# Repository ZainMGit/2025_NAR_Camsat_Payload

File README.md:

# 2025_NAR_CanSat_Payload
Download KiCAD_Camsat_PCB as a zip file and then open the project file within KiCAD to get the most up to date version of the pcb.

microsd pin orientation: 
-top view with pins pointing towards person and L to R- 
GND, VCC, MISO, MOSI, Sck, cs

9dof board
black wire - GND
Red - 3.3v 
blue- SDA
Yellow - SCL
order: BlaRBY

humidity - 
L to R with pins facing south
-GND, VCC, Signal

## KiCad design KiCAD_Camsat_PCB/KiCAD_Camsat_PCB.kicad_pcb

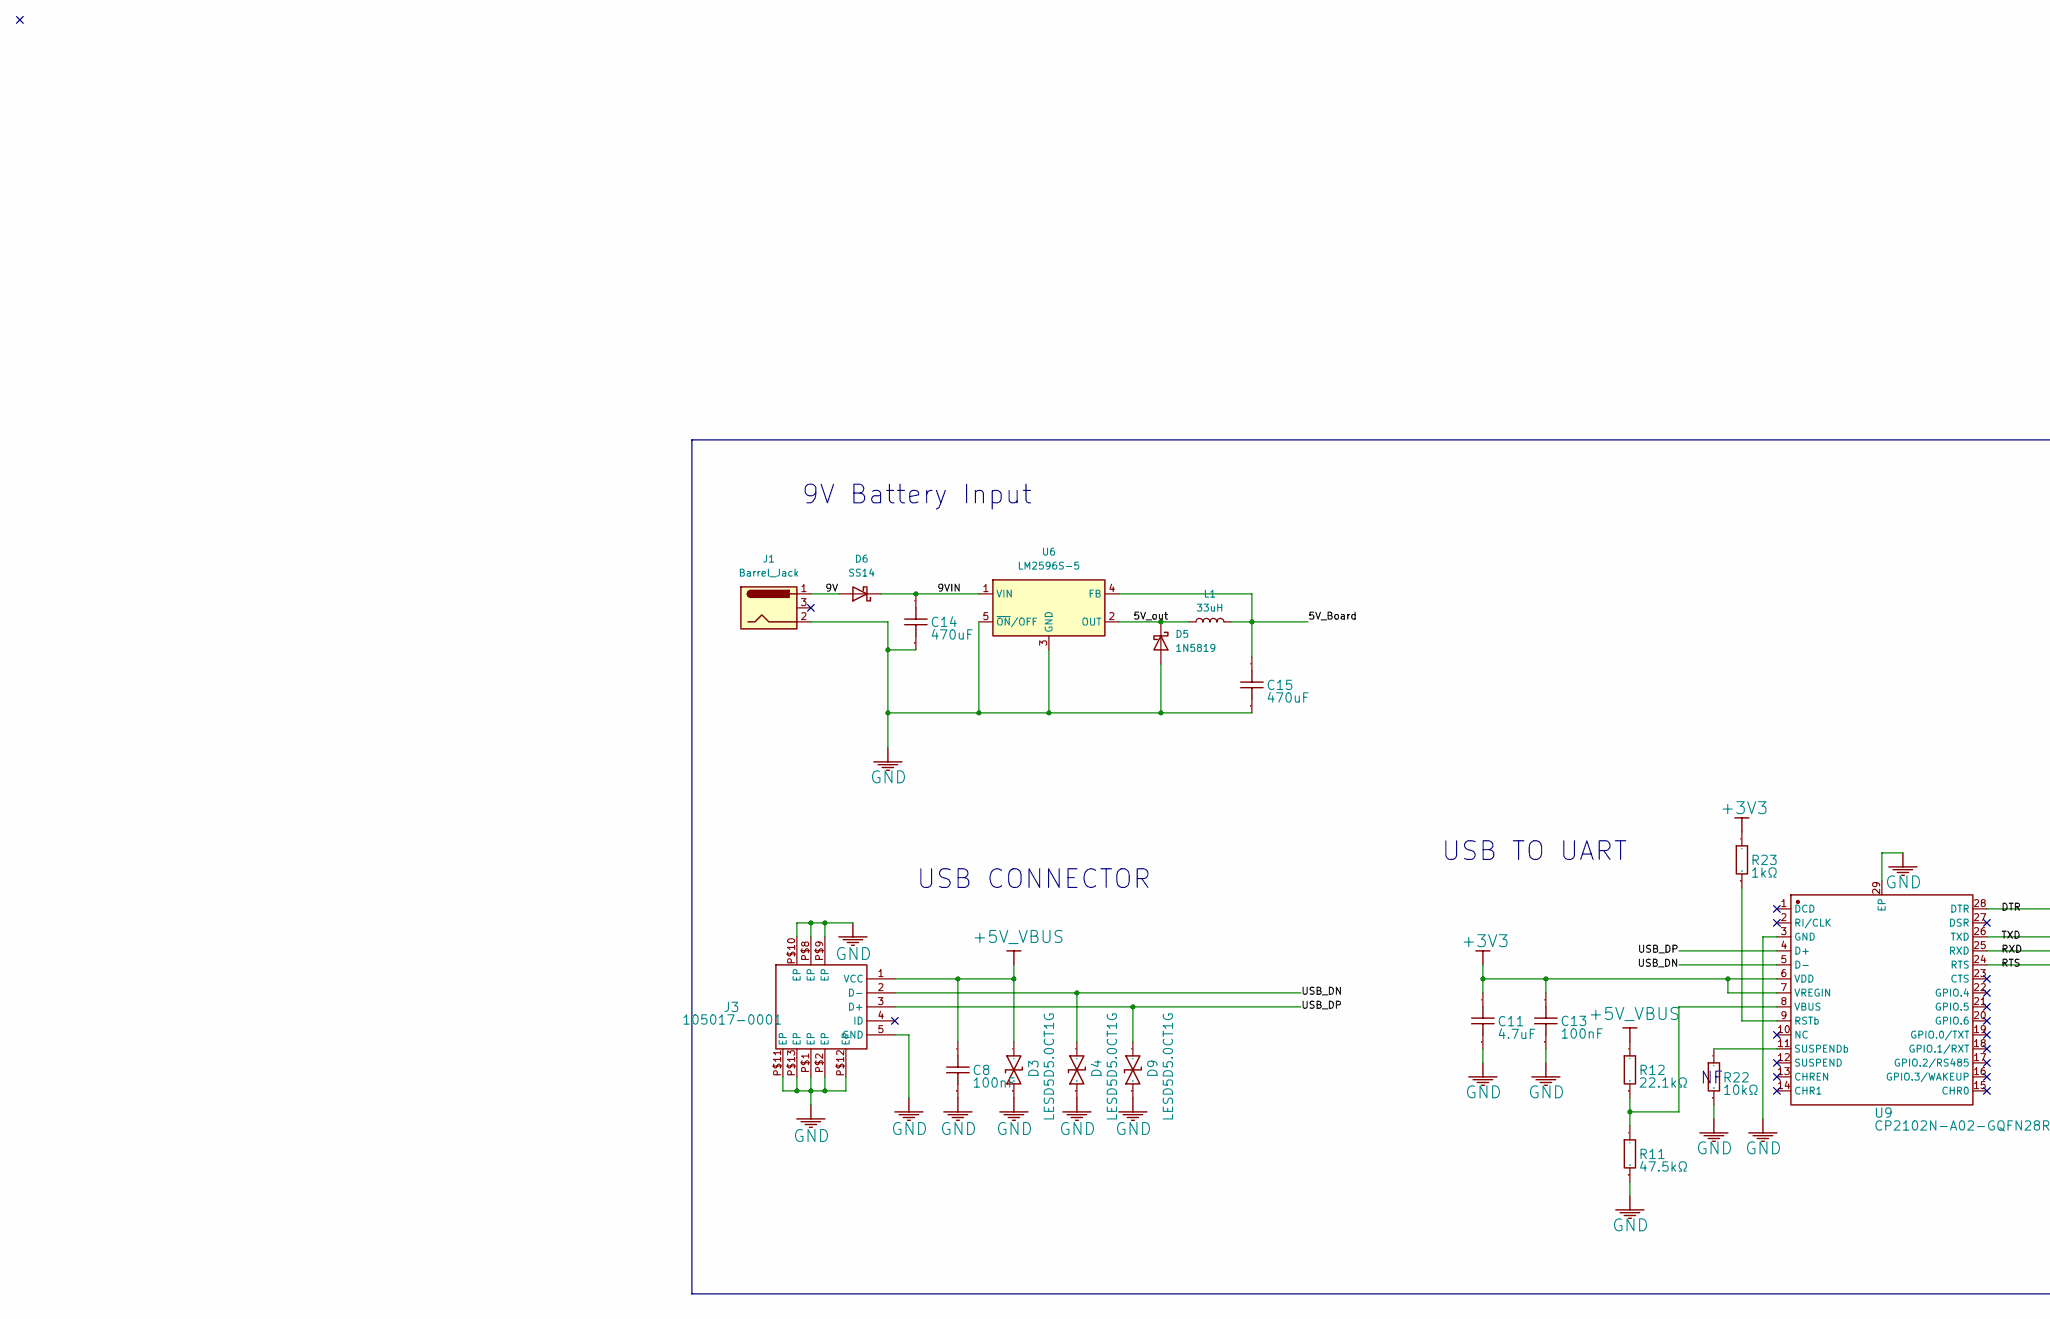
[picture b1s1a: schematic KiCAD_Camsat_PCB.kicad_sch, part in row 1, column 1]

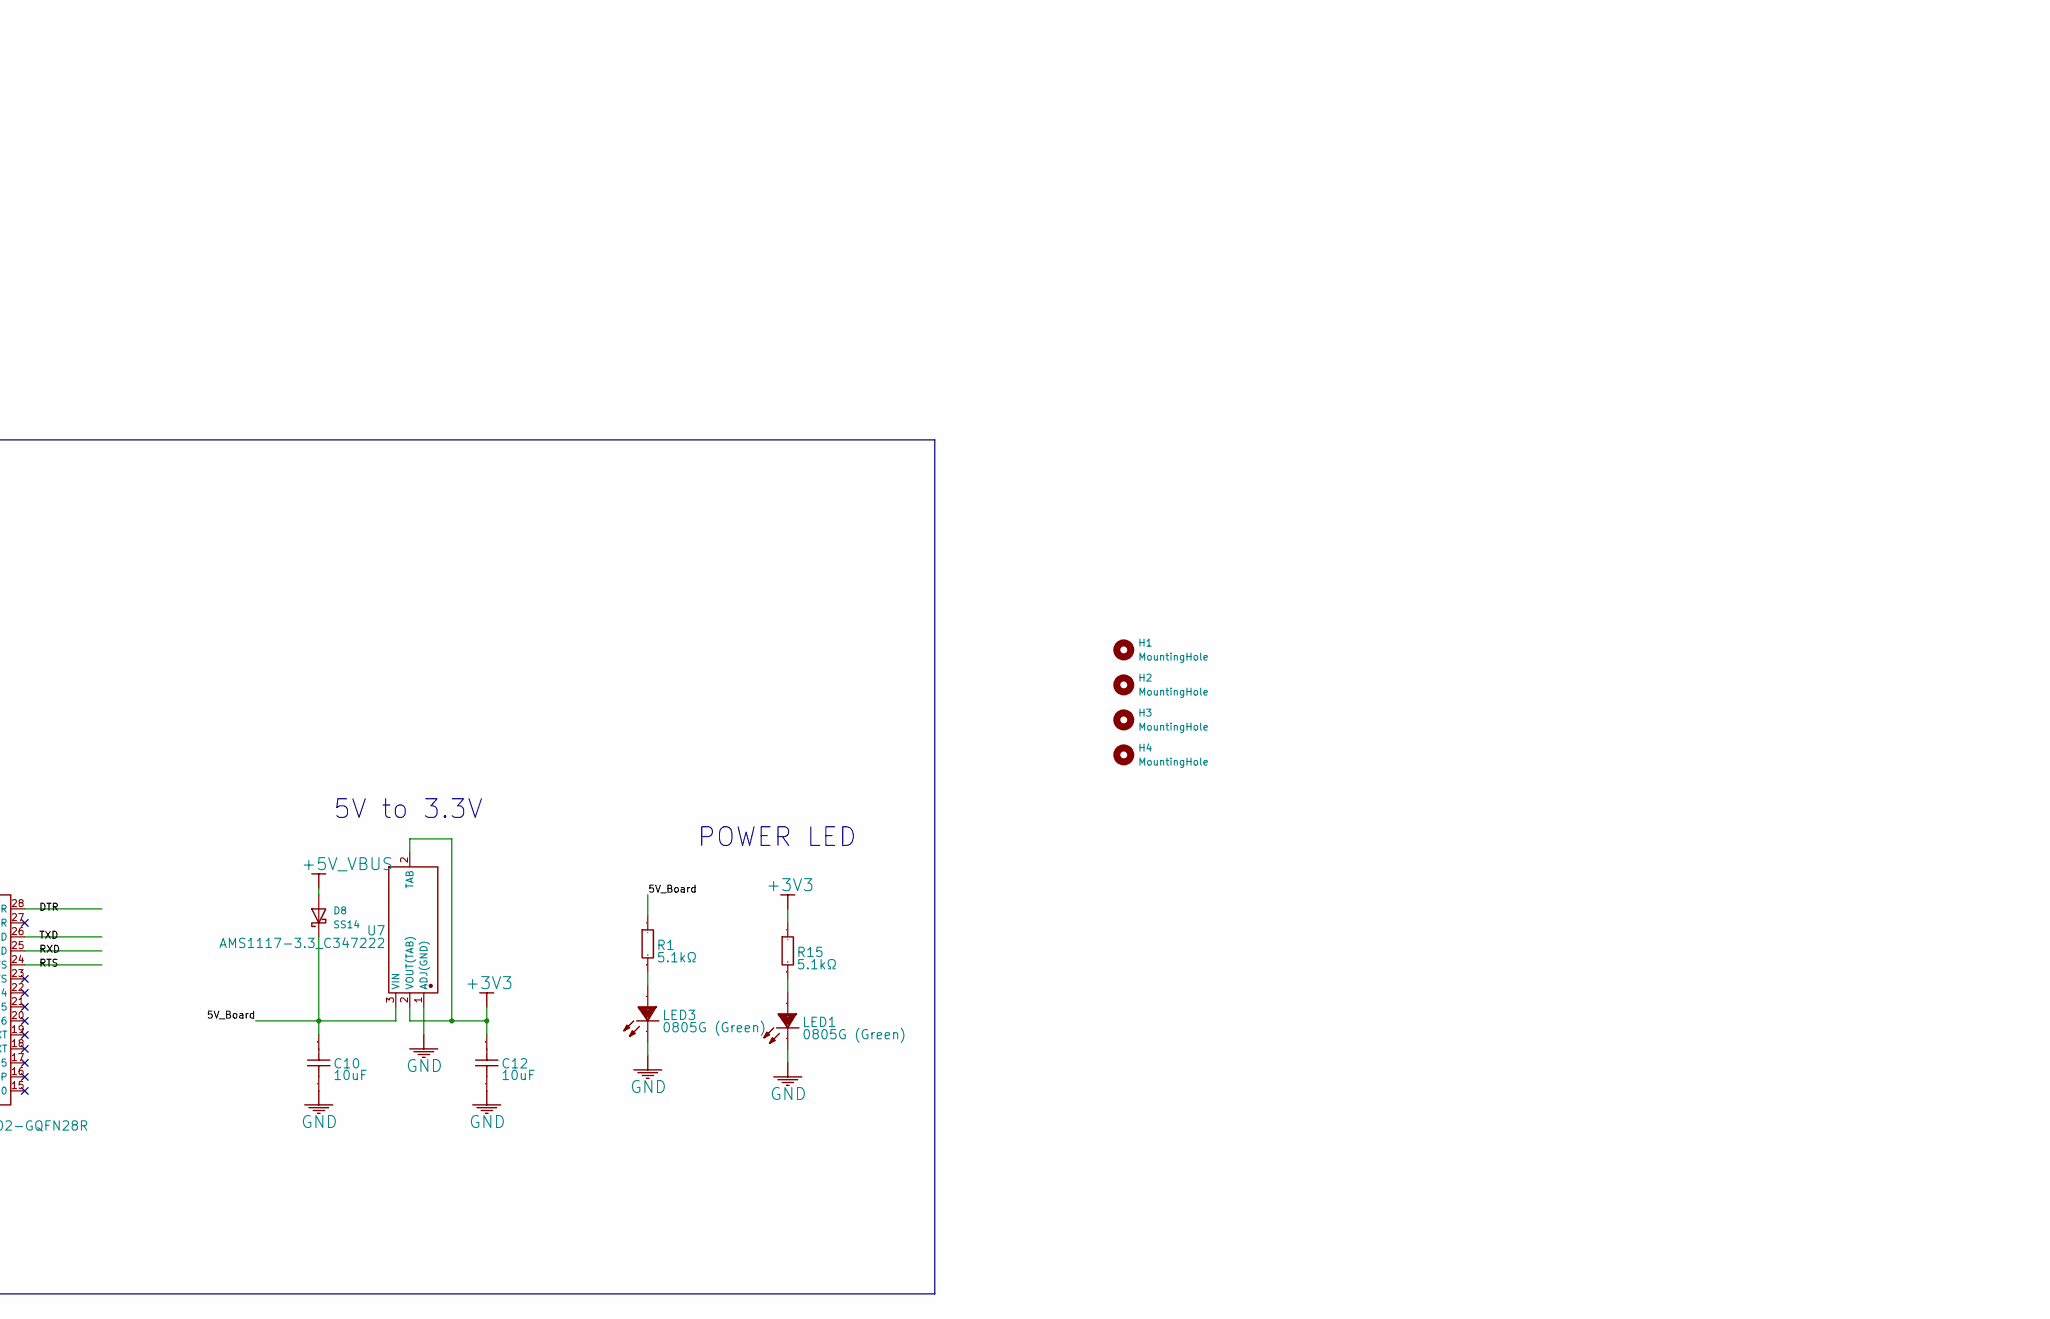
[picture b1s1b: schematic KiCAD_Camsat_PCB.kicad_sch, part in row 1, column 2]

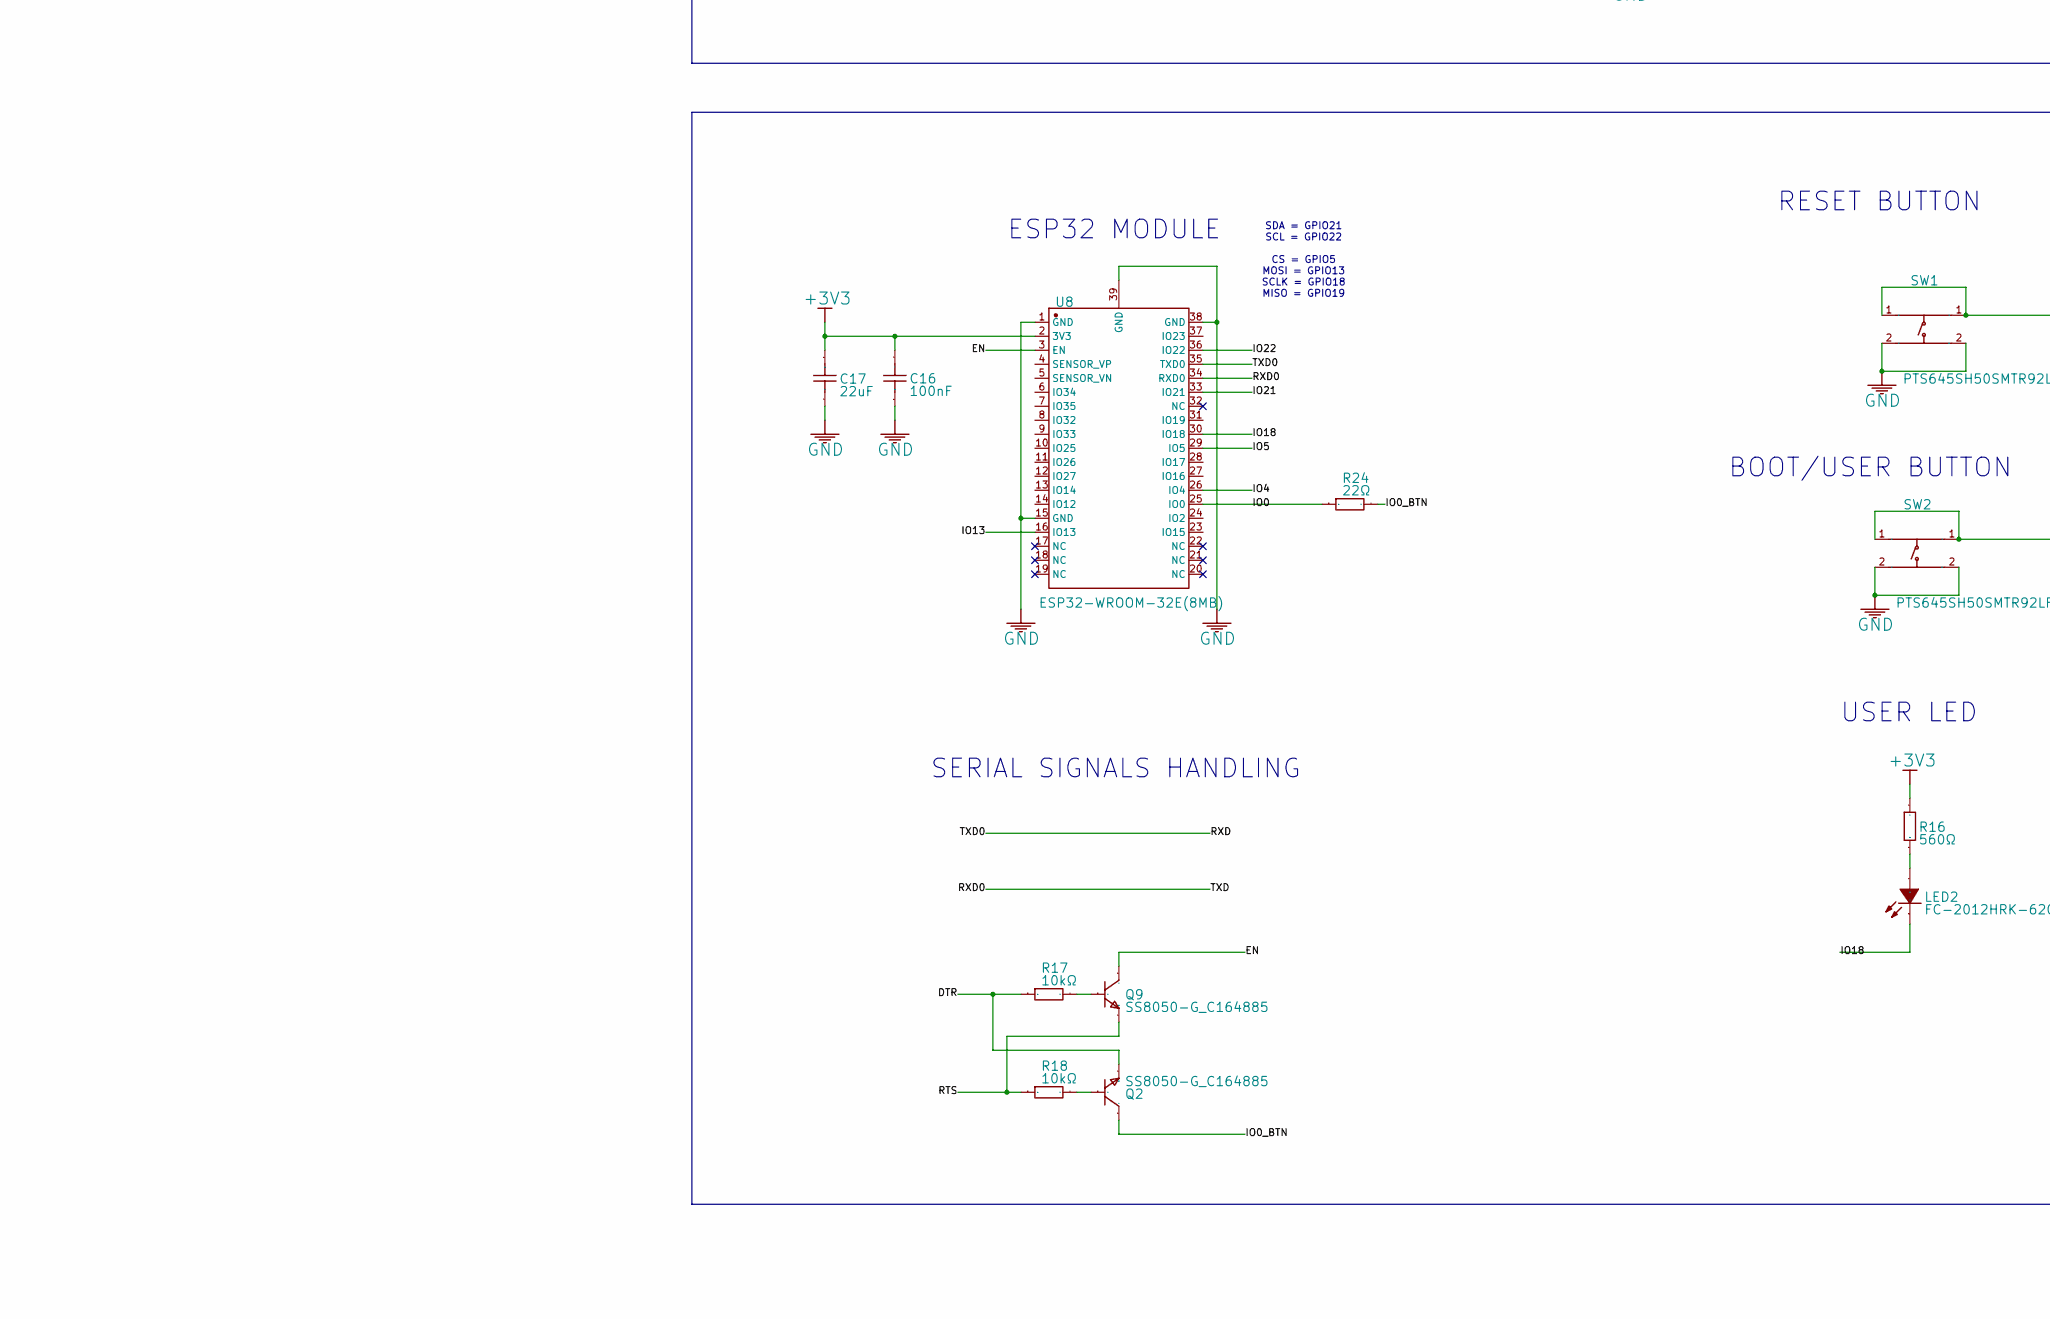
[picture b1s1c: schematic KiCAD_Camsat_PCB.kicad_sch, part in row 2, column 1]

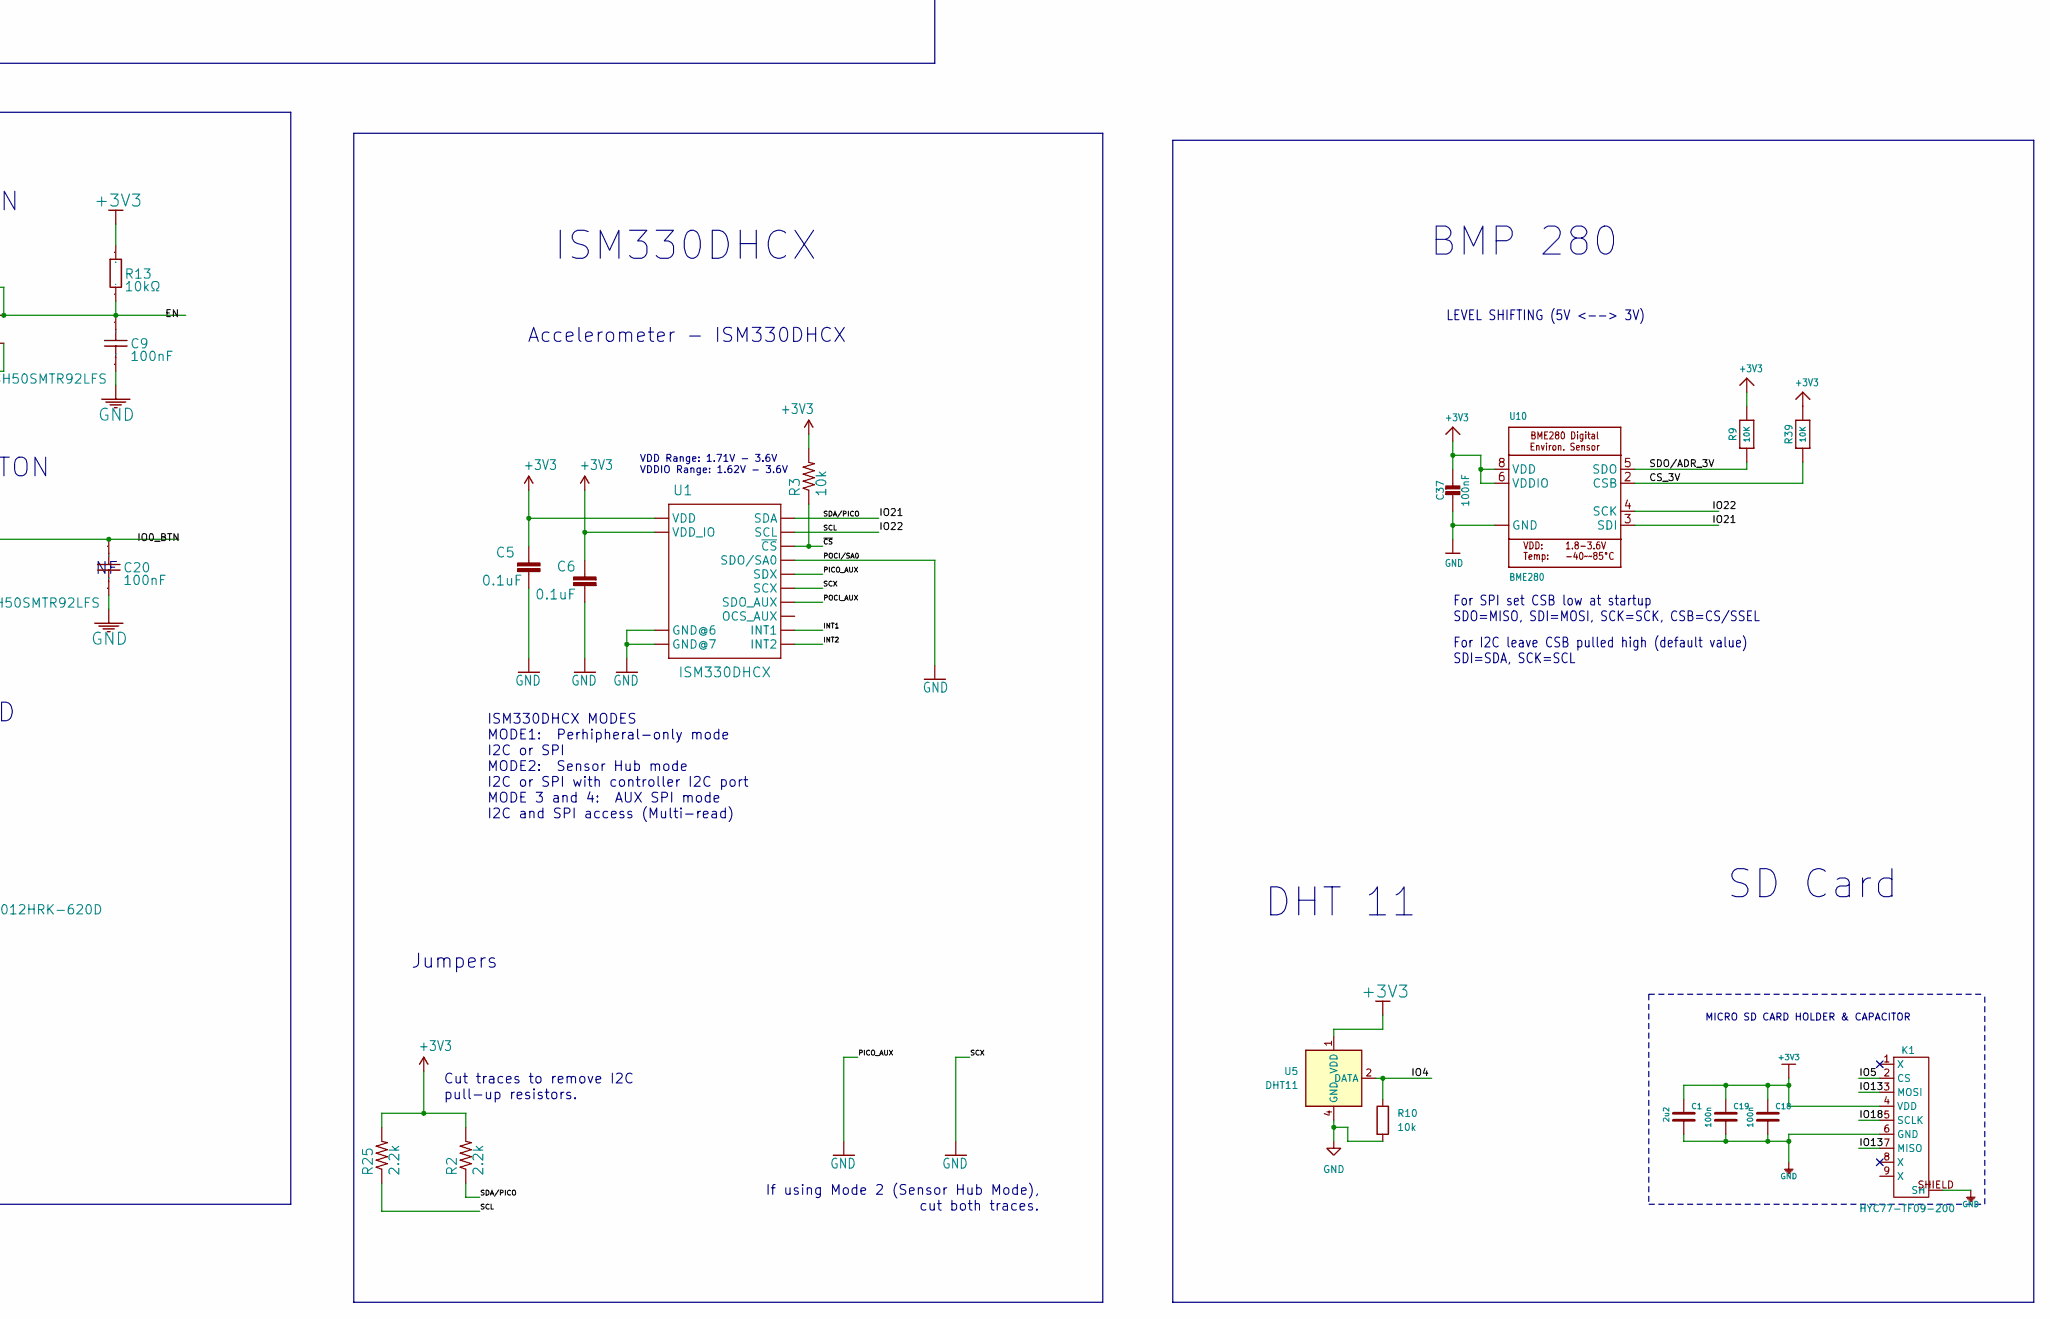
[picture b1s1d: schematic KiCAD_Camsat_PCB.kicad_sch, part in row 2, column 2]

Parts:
C1: 2u2; C_0603_1608Metric
C5, C6: 0.1uF; C_0603_1608Metric
C8, C9, C13, C16, C20: 100nF; C_0603_1608Metric; Manufacturer Part CL05B104KO5NNNC
C10, C12: 10uF; C_0805_2012Metric; Manufacturer Part CL05A106MP5NUNC
C11: 4.7uF; C_0805_2012Metric; Manufacturer Part CL05A475KP5NRNC
C14, C15: 470uF; C_0603_1608Metric; Manufacturer Part CL05B104KO5NNNC
C17: 22uF; C_1206_3216Metric; Manufacturer Part CL21A226MAYNNNE
C18, C19: 100n; C_0603_1608Metric
C37: 100nF; C_0603_1608Metric
D3, D4, D9: LESD5D5.0CT1G; D_SOD-523; Manufacturer Part LESD5D5.0CT1G
D5: 1N5819; D_DO-41_SOD81_P10.16mm_Horizontal
D6, D8: SS14; D_SMA
H1, H2, H3, H4: MountingHole; MountingHole_3mm
J1: Barrel_Jack; BarrelJack_CUI_PJ-102AH_Horizontal
J3: 105017-0001; MOLEX_105017-0001; Manufacturer Part 1050170001
K1: HYC77-TF09-200; MICROSD-HYC77-TF09-200
L1: 33uH; L_Bourns_SRN8040TA
LED1, LED3: 0805G (Green); LED_0805_2012Metric; Manufacturer Part KT-0805G
LED2: FC-2012HRK-620D; LED_0805_2012Metric; Manufacturer Part NCD0805R1
Q2, Q9: SS8050-G_C164885; SOT-23; Manufacturer Part SS8050-G(RANGE:200-350)
R1, R15: 5.1kΩ; R_0805_2012Metric; Manufacturer Part 0402WGF5101TCE
R2, R25: 2.2k; R_0805_2012Metric
R3, R10: 10k; R_0805_2012Metric
R9, R39: 10K; R_0805_2012Metric
R11: 47.5kΩ; R_0805_2012Metric; Manufacturer Part 0402WGF4752TCE
R12: 22.1kΩ; R_0805_2012Metric; Manufacturer Part 0402WGF2212TCE
R13, R17, R18, R22: 10kΩ; R_0805_2012Metric; Manufacturer Part 0402WGF1002TCE
R16: 560Ω; R_0805_2012Metric; Manufacturer Part 0402WGF5600TCE
R23: 1kΩ; R_0805_2012Metric; Manufacturer Part 0402WGF1001TCE
R24: 22Ω; R_0805_2012Metric; Manufacturer Part 0402WGF220JTCE
SW1, SW2: PTS645SH50SMTR92LFS; SW_SPST_PTS645Sx43SMTR92; Manufacturer Part PTS645SH50SMTR92LFS
U1: ISM330DHCX; PQFN50P250X300X86-14N
U5: DHT11; Aosong_DHT11_5.5x12.0_P2.54mm
U6: LM2596S-5; TO-263-5_TabPin3
U7: AMS1117-3.3_C347222; SOT-223-3_TabPin2; Manufacturer Part AMS1117-3.3
U8: ESP32-WROOM-32E(8MB); ESP32-WROOM-32E; Manufacturer Part ESP32-WROOM-32E-N8
U9: CP2102N-A02-GQFN28R; QFN-28-1EP_5x5mm_P0.5mm_EP3.35x3.35mm; Manufacturer Part CP2102N-A02-GQFN28R
U10: BME280; PSON65P250X250X100-8N

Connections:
+3V3: C1.2, C5.1, C6.1, C11.2, C12.1, C13.2, C16.2, C17.1, C18.2, C19.2, C37.1, K1.4 (VDD), R2.2, R3.2, R9.2, R13.1, R15.2, R16.2, R23.2, R25.2, R39.2, U1.5 (VDD_IO), U1.8 (VDD), U5.1 (VDD), U7.2 (VOUT(TAB)), U8.2 (3V3), U9.6 (VDD), U9.7 (VREGIN), U10.6 (VDDIO), U10.8 (VDD)
+5V_VBUS: C8.2, D3.2, D8.2 (A), J3.1 (VCC), R12.2
/5V_Board: C10.1, C15.2, D8.1 (K), L1.2, R1.2, U6.4 (FB), U7.3 (VIN)
/5V_out: D5.1 (K), L1.1, U6.2 (OUT)
/9V: D6.2 (A), J1.1
/9VIN: C14.2, D6.1 (K), U6.1 (VIN)
/CS_3V: R39.1, U10.2 (CSB)
/DTR: Q2.2 (E), R17.1, U9.28 (DTR)
/EN: C9.2, Q9.3 (C), R13.2, SW1.1, U8.3 (EN); also elsewhere on the board
/INT1: U1.4 (INT1)
/INT2: U1.9 (INT2)
/IO0: R24.1, U8.25 (IO0)
/IO0_BTN: C20.2, Q2.3 (C), R24.2, SW2.1; also elsewhere on the board
/IO4: R10.1, U5.2 (DATA), U8.26 (IO4)
/IO5: K1.2 (CS), U8.29 (IO5)
/IO13: K1.3 (MOSI), K1.7 (MISO), U8.16 (IO13)
/IO18: K1.5 (SCLK), LED2.1 (-), U8.30 (IO18); also elsewhere on the board
/IO21: R2.1, U1.14 (SDA), U8.33 (IO21), U10.3 (SDI)
/IO22: R25.1, U1.13 (SCL), U8.36 (IO22), U10.4 (SCK)
/POCI_AUX: U1.11 (SDO_AUX)
/RTS: Q9.2 (E), R18.1, U9.24 (RTS)
/RXD: U8.35 (TXD0), U9.25 (RXD)
/RXD0: U8.34 (RXD0), U9.26 (TXD)
/SDO/ADR_3V: R9.1, U10.5 (SDO)
/USB_DN: D4.2, J3.2 (D-), U9.5 (D-)
/USB_DP: D9.2, J3.3 (D+), U9.4 (D+)
/~CS: R3.1, U1.12 (~CS)
GND: C1.1, C5.2, C6.2, C8.1, C9.1, C10.2, C11.1, C12.2, C13.1, C14.1, C15.1, C16.1, C17.2, C18.1, C19.1, C20.1, C37.2, D3.1, D4.1, D5.2 (A), D9.1, J1.2, J3.5 (GND), J3.P$1 (EP), J3.P$2 (EP), J3.P$8 (EP), J3.P$9 (EP), J3.P$10 (EP), J3.P$11 (EP), J3.P$12 (EP), J3.P$13 (EP), K1.6 (GND), K1.SHIELD (SH), LED1.2 (K), LED3.2 (K), R10.2, R11.1, R22.1, SW1.2 (3), SW2.2 (3), U1.1 (SDO/SA0), U1.2 (SDX), U1.3 (SCX), U1.6 (GND@6), U1.7 (GND@7), U5.4 (GND), U6.3 (GND), U6.5 (~ON/OFF), U7.1 (ADJ(GND)), U8.1 (GND), U8.15 (GND), U8.38 (GND), U8.39 (GND), U9.3 (GND), U9.29 (EP), U10.1 (GND), U10.7 (GND); also elsewhere on the board
unnamed: LED1.1 (A), R15.1
unnamed 29: LED2.2 (+), R16.1; also elsewhere on the board
unnamed: LED3.1 (A), R1.1
unnamed: Q2.1 (B), R18.2
unnamed: Q9.1 (B), R17.2
unnamed: R23.1, U9.9 (RSTb)
unnamed: R22.2, U9.11 (SUSPENDb)
unnamed: R11.2, R12.1, U9.8 (VBUS)

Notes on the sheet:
ESP32 MODULE
SDA = GPIO21 SCL = GPIO22 CS = GPIO5 MOSI = GPIO13 SCLK = GPIO18 MISO = GPIO19
DHT 11
SD Card
POWER LED
BOOT/USER BUTTON
VDD Range: 1.71V - 3.6V VDDIO Range: 1.62V - 3.6V
9V Battery Input
MICRO SD CARD HOLDER & CAPACITOR
ISM330DHCX MODES MODE1: Perhipheral-only mode I2C or SPI MODE2: Sensor Hub mode I2C or SPI with controller I2C port MODE 3 and 4: AUX SPI mode I2C and SPI access (Multi-read)
USB CONNECTOR
SERIAL SIGNALS HANDLING
For I2C leave CSB pulled high (default value) SDI=SDA, SCK=SCL
USB TO UART
USER LED
5V to 3.3V
For SPI set CSB low at startup SDO=MISO, SDI=MOSI, SCK=SCK, CSB=CS/SSEL
LEVEL SHIFTING (5V <--> 3V)
BMP 280
ISM330DHCX
Jumpers
RESET BUTTON
Cut traces to remove I2C pull-up resistors.
Accelerometer - ISM330DHCX
If using Mode 2 (Sensor Hub Mode), cut both traces.

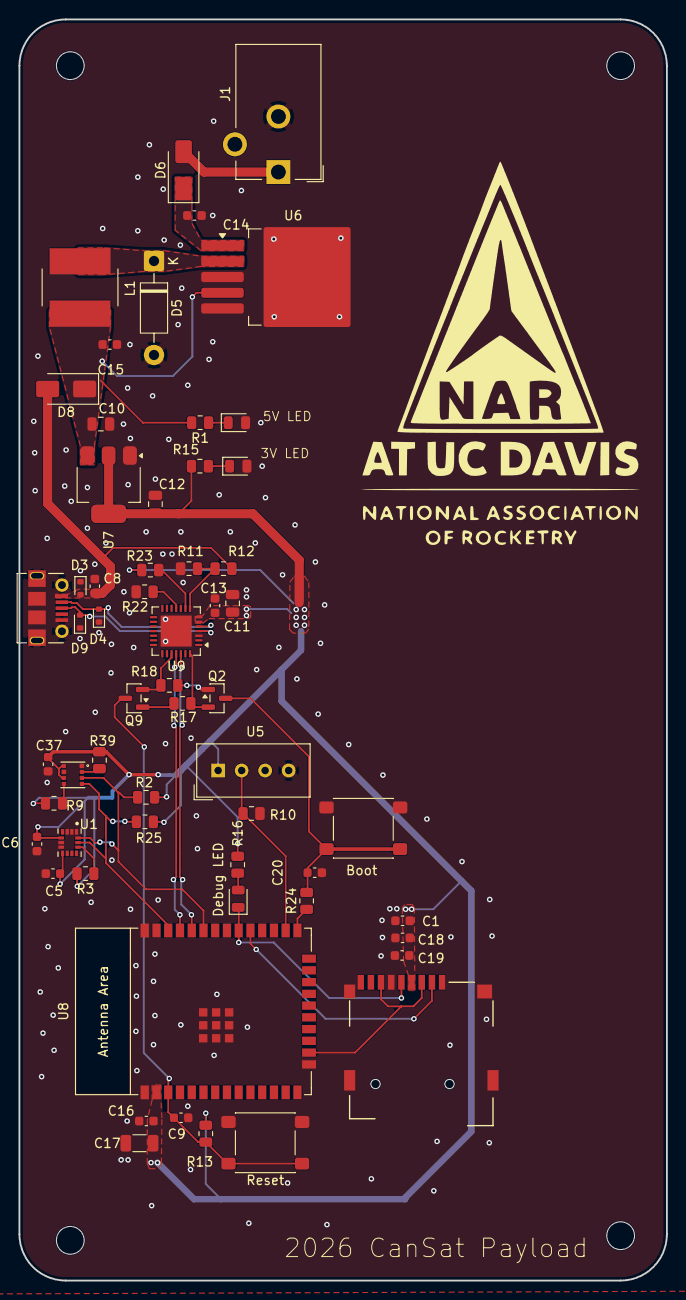
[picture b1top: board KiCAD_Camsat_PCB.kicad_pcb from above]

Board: 2 copper layers, 70.0 x 136.3 mm, 62 parts (0 on the bottom side), 33 nets.

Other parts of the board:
Boot: PTS645SH50SMTR92LFS; SW_SPST_PTS645Sx43SMTR92
Debug LED: FC-2012HRK-620D; LED_0805_2012Metric
Reset: PTS645SH50SMTR92LFS; SW_SPST_PTS645Sx43SMTR92

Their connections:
/EN: Reset.1; also elsewhere on the board
/IO0_BTN: Boot.1; also elsewhere on the board
/IO18: Debug LED.1 (-); also elsewhere on the board
GND: Boot.2 (3), Reset.2 (3); also elsewhere on the board
unnamed 29: Debug LED.2 (+); also elsewhere on the board

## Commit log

2026-02-08 Add symbol files
2026-02-08 Add KiCAD Project
2026-02-10 Create Prototype_program
2026-02-10 DHT11 Integration
2026-02-10 Update README.md
    description of sensor pins with pins facing south
2026-02-10 README.md
2026-03-03 Small Bug Fixes
2026-03-03 Pin Change
2026-03-27 Payload_PCB files
2026-04-01 Payload pcb updates
2026-04-01 Schematic updates
2026-04-07 9V connector
2026-04-07 Footprint Updates
2026-04-07 All Footprints completed
2026-04-09 schemaric errors
2026-04-09 Power selection
2026-04-14 Schematic Ready
2026-04-14 New PCB design
2026-04-21 traces
2026-04-25 PCB changes
2026-04-25 Prototype
2026-04-25 FInal proto changes
2026-04-29 new changes
2026-04-29 DRC update
2026-04-29 file organization
2026-04-30 Layout Revision
    Removed unnecessary nets.
    Added nets for copper pours.
    Removed some non-critical components from schematic.
    Still needs some extra vias and adjusting silkscreen.
2026-05-01 PCB Board Updates
    - Board Dimensions changed to 70mm width
    - Descriptive Silkscreen values added
2026-05-01 More silkscreen updates
2026-05-01 silkscreen update
2026-05-02 Mounting Hole Size Changes
2026-05-04 Fix project name typo in README
2026-05-04 Final Design Changes
    - Updated Silkscreen
    - small route updates
